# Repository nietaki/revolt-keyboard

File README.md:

[ ](https://discord.gg/myEkxF7rhV)

# Revolt Keyboard

> **Revolt** - a split ergonomic keyboard prioritising ease of adoption, flexibilty, easy build+repair, and partial upgrades
> 

## Why call it “Revolt”?

1. It’s heavily inspired by [Redox](https://github.com/mattdibi/redox-keyboard), an amazing open-source keyboard, that is still my daily driver
2. It’s revolting against the popular design philosophy of keybords like Sofle, Lily58 or Corne, which prioritise a compact footprint over other qualities
3. Some might find it “revolting”, since its looks are secondary to its features

More info on the design philosophy behind revolt in the [Revolt Manifesto](./Revolt_Manifesto.md)

## TL;DR

It’s a 68(+3) key, wired, choc-based split ergonomic keyboard running QMK. Instead of being split into 2 halves, it’s split into 3 parts: left input, right input and the center one called “commander”

The left and right input parts are “dumb”, and contain only the switches and diodes to make 7x5 matrix work, plus optional LEDs under home keys.

The case will be made with low profile + tenting in mind (with multiple tenting angles possible), with two versions: for soldered switches without a top plate and hotswap with a top plate.

The commander board should lend itself to experimenting with different pointing devices. 
Current has connectors for a PSP 3000 joystick. It should be easy to create versions that support other pointing devises, like a trackball, a Cirque touchpad or other joysticks.

## How To...

### ...build the keyboard?

Follow the [build video](https://www.youtube.com/watch?v=ghhF0bAFxww). You can find more support under the links [here](https://ntkstudio.net/products/revolt-keyboard/#support).

### ...make the cases?

The case files are available on [Printables](https://www.printables.com/model/1439208-revolt-keyboard-cases-rev1) and [Thingiverse](https://www.thingiverse.com/thing:7166363).

### ...compile the firmware?

```bash
$ cd /path/to/qmk_firmware
$ qmk compile -kb revolt/rev1 -km default
#  It should generate the firmware file
$ stat ./revolt_rev1_default.uf2
```
### ...flash the firmware?

1. Unplug the commander board
1. Push the `bootsel` button on the RP2040
1. While having the button pushed in, connect the commander board to the computer

A virtual drive (?) for the rpi should be discovered by the computer. 
Drag the compiled firmware file into it. 
RPi will reboot and run the firmware.

## FAQ

### Why do you hate Sofle/Lily58/Corne?

I don’t! They’re beautiful keyboards, designed with love and forethought, all of them with passionate communities. They just don’t fit the criteria of what I’m looking for in an ergonomic keyboard that can be used just as easily for programming and gaming, especially for people coming from “regular” keyboards. I wanted to make a keyboard that’s perfect for me and other like-minded people.

### No wireless version?

I’m not ruling out a wireless version in the future. I’d like to perfect the wired version to my liking and see what kinds of compromises make sense.

But with Revolt being open source, there’s no reason for anyone interested not to take a crack at it themselves.

## Workflow

1. Build matrix, outline and pcb in yml
2. generate kicad pcb
3. Create the kicad project
4. Replace the kicad pcb file with the generated one
5. Replace the switch footprints with the ones from keyswitch library
5. Create the matrix schematic by hand, with the diode numbers matching the swich numbers from pcb
6. **change the diode numbers in the pcb to line up with the switch numbers in the pcbnew**
  - this can be automated together with the switch numbers, I think
7. Add hierarchical net names
7. Update the schematic from the pcb band the other way until stuff is consistent.
8. ...
8. Draw the rest of the owl

## Special thanks

Projects that helped or inspired me:

- https://github.com/mattdibi/redox-keyboard
- https://github.com/daprice/keyswitches.pretty/ - adapted some footprints from this brilliant library
- https://flatfootfox.com/ergogen-introduction/
- https://github.com/labtroll/KiCad-DesignRules/tree/main
- https://docs.ergogen.xyz/
- https://github.com/sol/KiCad-RP-Pico

## License

[Revolt Keyboard](https://github.com/nietaki/revolt-keyboard)© 2024 by [@nietaki](https://nietaki.com/) is licensed under [CC BY-SA 4.0](http://creativecommons.org/licenses/by-sa/4.0/?ref=chooser-v1)

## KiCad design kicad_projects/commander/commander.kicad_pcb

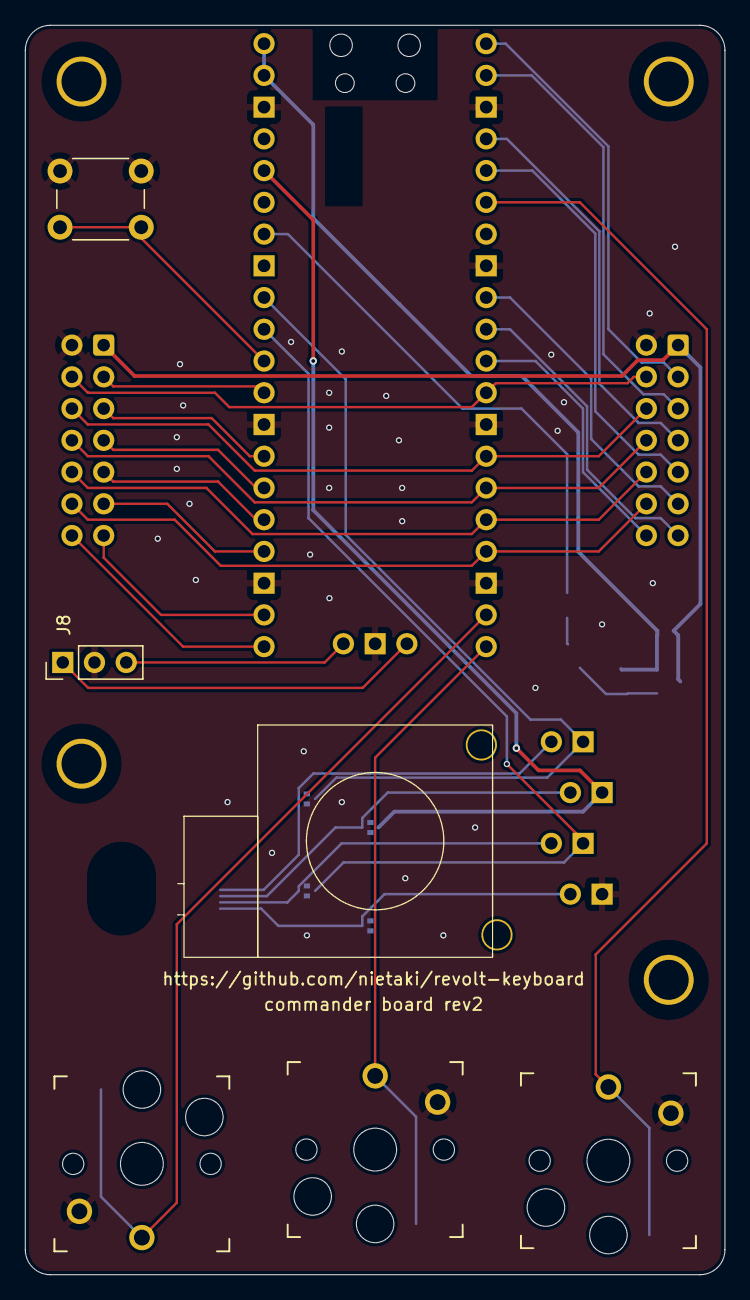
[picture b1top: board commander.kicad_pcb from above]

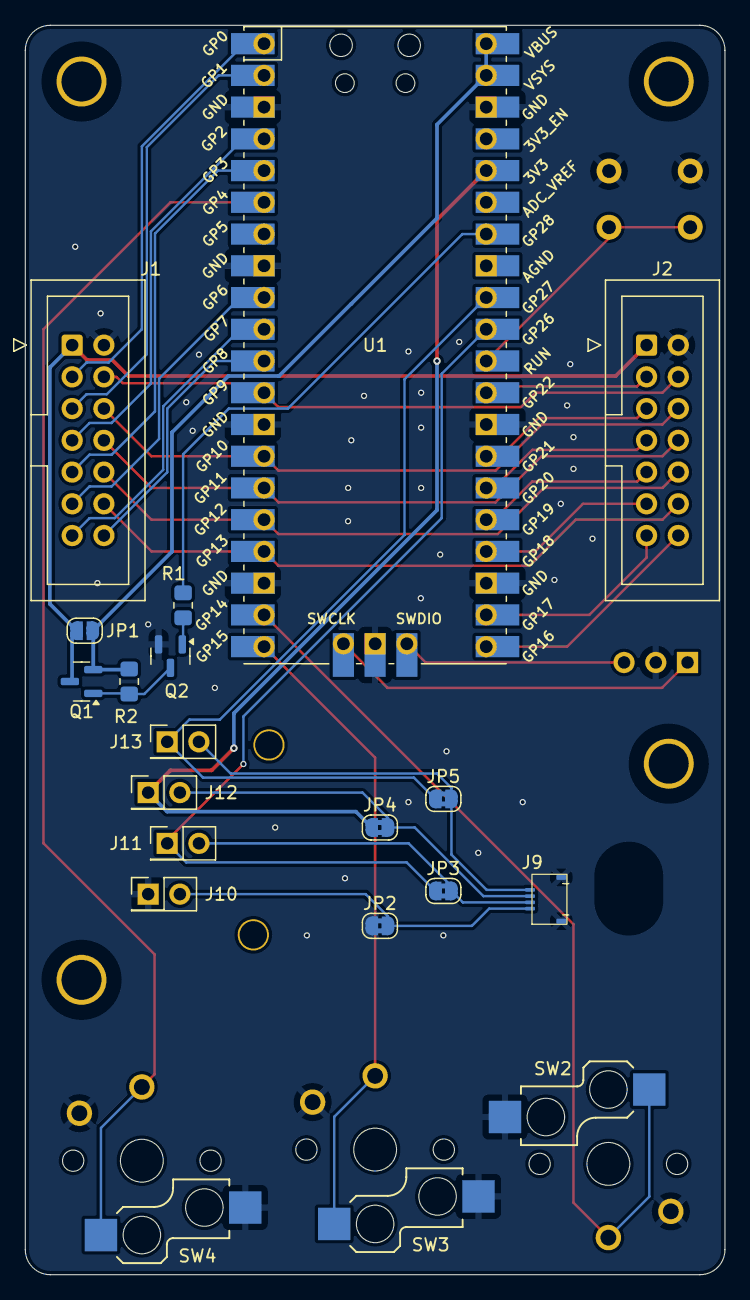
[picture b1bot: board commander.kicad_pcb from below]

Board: 2 copper layers, 56.0 x 100.0 mm, 27 parts (17 on the bottom side), 38 nets.

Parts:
HOLE_M3, HOLE_M3#2, HOLE_M3#3: H2; HOLE_M3
HOLE_M3#4: H1; HOLE_M3
J1: right input IDC14; IDC-Header_2x07_P2.54mm_Vertical
J2: left input IDC14; IDC-Header_2x07_P2.54mm_Vertical
J8: debug out; PinHeader_1x03_P2.54mm_Vertical
J9: HC-FPC-05-09-4RLTAG
J10, J11, J12, J13: Conn_02x01; PinHeader_2x01_P2.54mm_Vertical
JP1: SolderJumper_2_Open; SolderJumper-2_P1.3mm_Open_RoundedPad1.0x1.5mm
JP2, JP3, JP4, JP5: SolderJumper_2_Bridged; SolderJumper-2_P1.3mm_Bridged2Bar_RoundedPad1.0x1.5mm
PSP_JOY: PSP1000_JOY
Q1: AO3401A; SOT-23
Q2: NPN - MMBT2222A; SOT-23
R1: 1k; R_0805_2012Metric_Pad1.20x1.40mm_HandSolder
R2: 10k; R_0805_2012Metric_Pad1.20x1.40mm_HandSolder
SW1: RESET_SWITCH; SW_PUSH_6mm_H4.3mm
SW2, SW3, SW4: SW_Push; Kailh_socket_PG1350_optional
U1: Pico; RPi_Pico_SMD_TH

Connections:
3V3: J12.1, JP4.1 (A), U1.36 (3V3)
5V: JP1.1 (A), Q1.2 (S), R2.2, U1.39 (VSYS), U1.40 (VBUS)
/COL0: J2.3, U1.29 (GPIO22)
/COL1: J2.5, U1.27 (GPIO21)
/COL2: J2.7, U1.26 (GPIO20)
/COL3: J2.9, U1.25 (GPIO19)
/COL4: J2.11, U1.24 (GPIO18)
/COL5: J2.13, U1.22 (GPIO17)
/COL6: J2.14, U1.21 (GPIO16)
/COL7: J1.14, U1.11 (GPIO8)
/COL8: J1.13, U1.10 (GPIO7)
/COL9: J1.11, U1.9 (GPIO6)
/COL10: J1.9, U1.5 (GPIO3)
/COL11: J1.7, U1.4 (GPIO2)
/COL12: J1.5, U1.2 (GPIO1)
/COL13: J1.3, U1.1 (GPIO0)
/LED_ENABLE: R1.2, U1.34 (GPIO28_ADC2)
/LMB: SW2.1, U1.19 (GPIO14)
/MMB: SW3.1, U1.20 (GPIO15)
/RMB: SW4.1, U1.6 (GPIO4)
/ROW0: J1.12, J2.12, U1.17 (GPIO13)
/ROW1: J1.10, J2.10, U1.16 (GPIO12)
/ROW2: J1.8, J2.8, U1.15 (GPIO11)
/ROW3: J1.6, J2.6, U1.14 (GPIO10)
/ROW4: J1.4, J2.4, U1.12 (GPIO9)
/RUN: SW1.2, U1.30 (RUN)
/X1: J11.1, JP3.1 (A), U1.31 (GPIO26_ADC0)
/X2: J13.1, JP5.1 (A), U1.32 (GPIO27_ADC1)
GND: J1.2, J2.2, J8.2, J9.5 (P1), J9.6 (P2), J10.1, JP2.1 (A), Q2.2 (E), SW1.1, SW2.2, SW3.2, SW4.2, U1.3 (GND), U1.8 (GND), U1.13 (GND), U1.18 (GND), U1.23 (GND), U1.28 (GND), U1.38 (GND), U1.42 (GND)
LED_5V: J1.1, J2.1, JP1.2 (B), Q1.3 (D)
unnamed: J8.1, U1.41 (SWCLK)
unnamed: J8.3, U1.43 (SWDIO)
unnamed: J9.1, J10.2, JP2.2 (B)
unnamed: J9.2, J11.2, JP3.2 (B)
unnamed: J9.3, J12.2, JP4.2 (B)
unnamed: J9.4, J13.2, JP5.2 (B)
unnamed: Q1.1 (G), Q2.3 (C), R2.1
unnamed: Q2.1 (B), R1.1

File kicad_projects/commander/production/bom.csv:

Designator,Footprint,Quantity,Value,LCSC Part #
J1,IDC-Header_2x07_P2.54mm_Vertical,1,right input IDC14,
"J10, J11, J12, J13",PinHeader_2x01_P2.54mm_Vertical,4,Conn_02x01,
J2,IDC-Header_2x07_P2.54mm_Vertical,1,left input IDC14,
J8,PinHeader_1x03_P2.54mm_Vertical,1,debug out,
J9,HC-FPC-05-09-4RLTAG,1,522710469,
JP1,SolderJumper-2_P1.3mm_Open_RoundedPad1.0x1.5mm,1,SolderJumper_2_Open,
PSP_JOY,PSP1000_JOY,1,PSP1000_JOY,
Q1,SOT-23,1,AO3401A,C15127
Q2,SOT-23,1,NPN - MMBT2222A,C8512
R1,0805,1,1k,
R2,0805,1,10k,
SW1,SW_PUSH_6mm_H4.3mm,1,RESET_SWITCH,
"SW2, SW3, SW4",Kailh_socket_PG1350_optional,3,SW_Push,
U1,RPi_Pico_SMD_TH,1,Pico,

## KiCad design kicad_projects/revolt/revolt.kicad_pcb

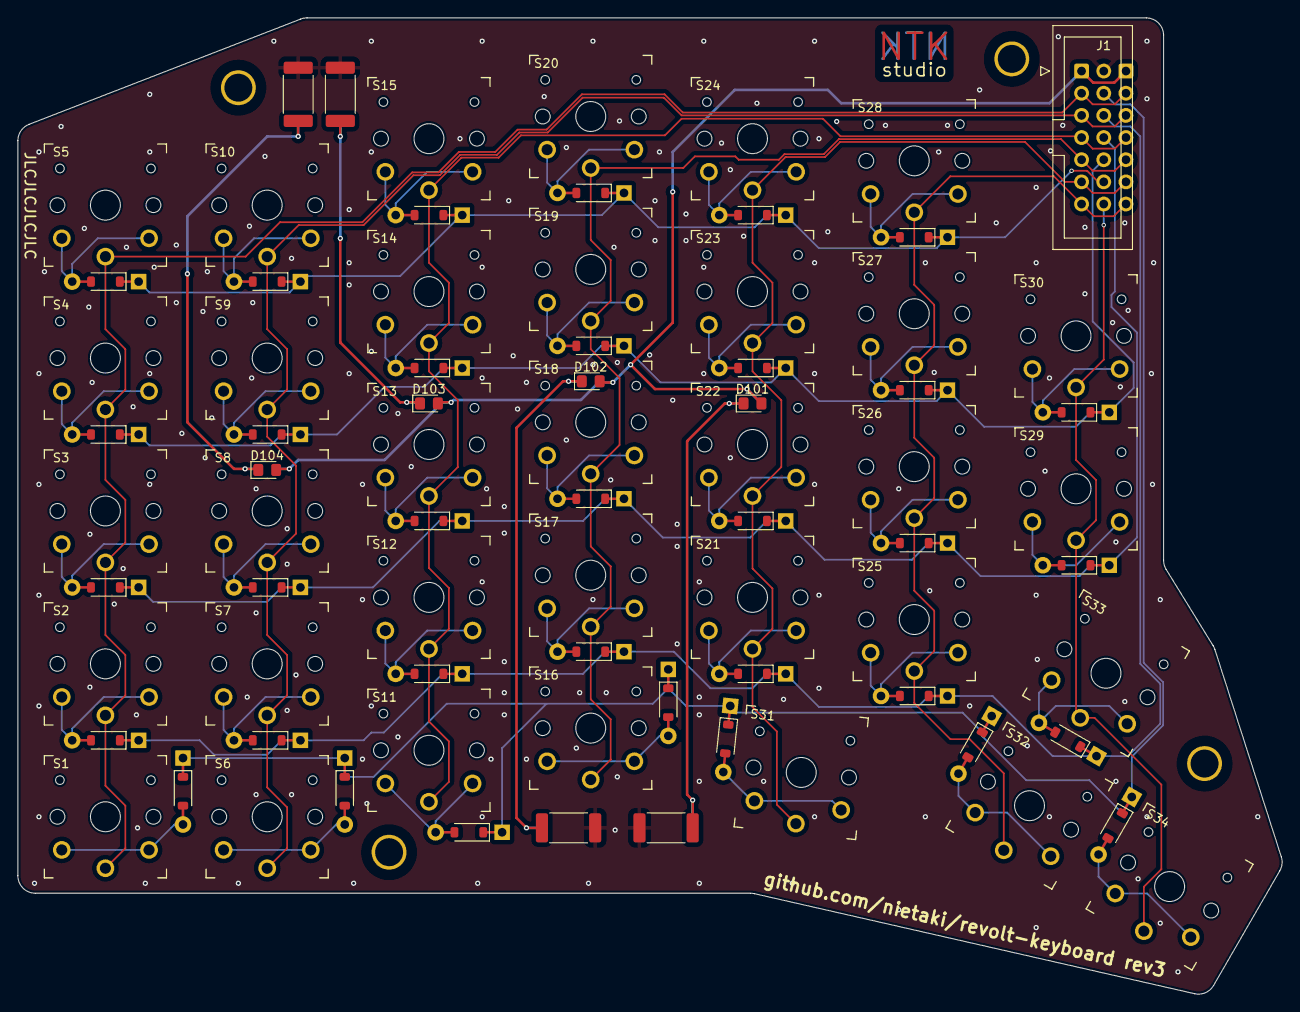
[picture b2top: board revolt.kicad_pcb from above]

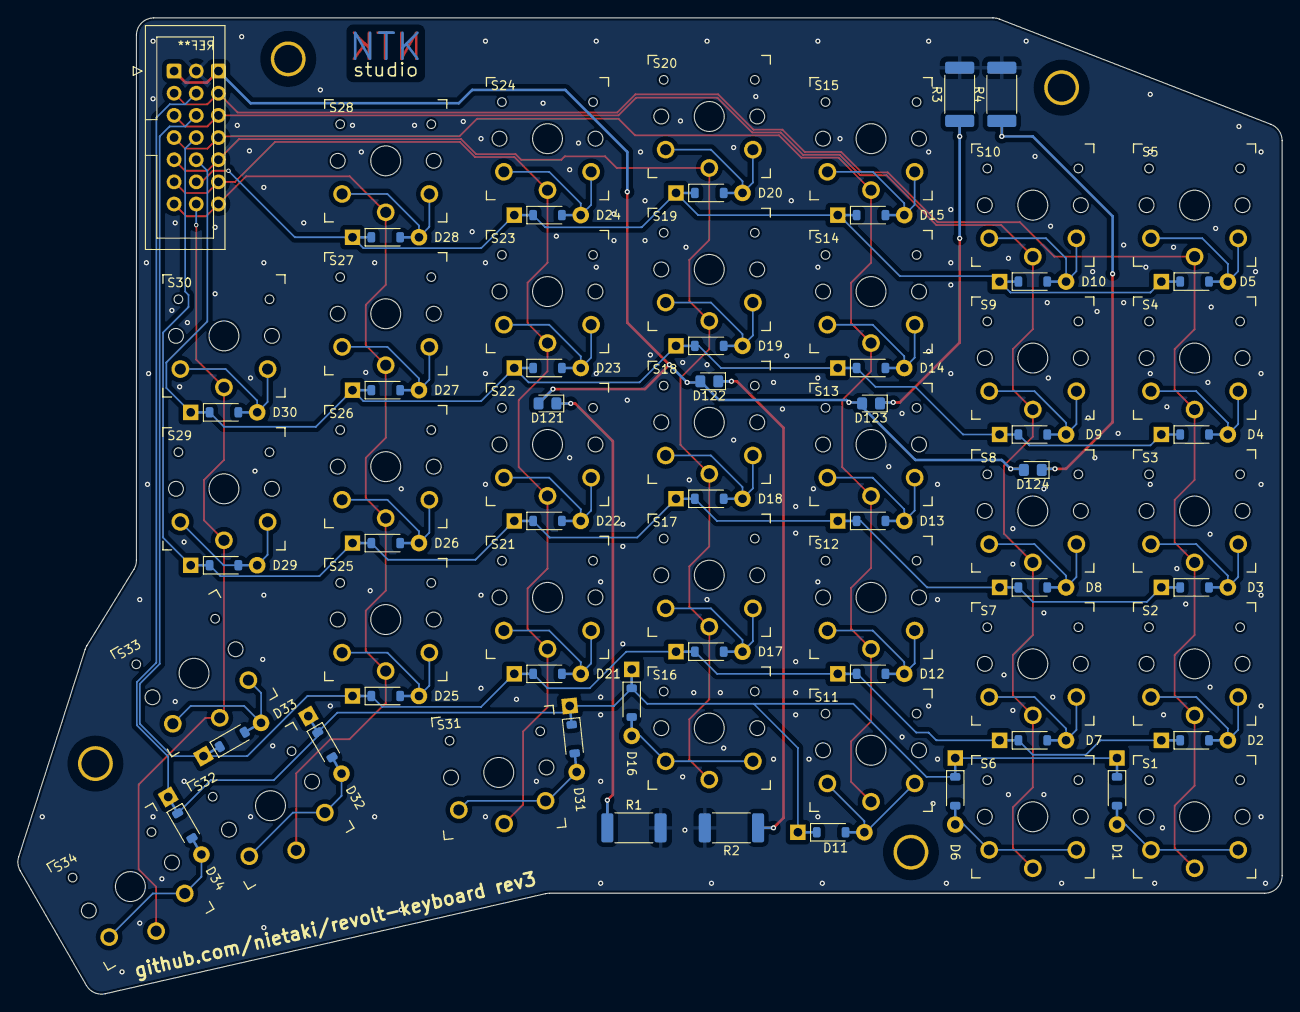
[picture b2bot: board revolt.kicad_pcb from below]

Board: 2 copper layers, 144.9 x 111.9 mm, 85 parts (42 on the bottom side), 52 nets.

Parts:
D1, D2, D3, D4, D5, D6, D7, D8, D9, D10, D11, D12, D13, D14, D15, D16, D17, D18, D19, D20, D21, D22, D23, D24, D25, D26, D27, D28, D29, D30, D31, D32, D33, D34: D_SOD-123-combo-reversible
D101, D102, D103, D104, D121, D122, D123, D124: LED; LED_0805_2012Metric_Pad1.15x1.40mm_HandSolder
H1, H2, H3, H4: MountingHole; HOLE_M3
J1: IDC-Header_2x07_P2.54mm_Vertical_Reversible
R1, R2, R3, R4: 150; R_2512_6332Metric_Pad1.40x3.35mm_HandSolder_reversible
S1, S2, S3, S4, S5, S6, S7, S8, S9, S10, S11, S12, S13, S14, S15, S16, S17, S18, S19, S20, S21, S22, S23, S24, S25, S26, S27, S28, S29, S30, S31, S32, S33, S34: SW_PG1350_reversible_with_keycap_outline

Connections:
5V: D101.2 (A), D102.2 (A), D103.2 (A), D104.2 (A), D121.2 (A), D122.2 (A), D123.2 (A), D124.2 (A), J1.1
/COL0: J1.3, S1.1, S2.1, S3.1, S4.1, S5.1
/COL1: J1.5, S6.1, S7.1, S8.1, S9.1, S10.1
/COL2: J1.7, S11.1, S12.1, S13.1, S14.1, S15.1
/COL3: J1.9, S16.1, S17.1, S18.1, S19.1, S20.1
/COL4: J1.11, S21.1, S22.1, S23.1, S24.1, S31.1
/COL5: J1.13, S25.1, S26.1, S27.1, S28.1, S32.1
/COL6: J1.14, S29.1, S30.1, S33.1, S34.1
/ROW0: D5.1 (K), D10.1 (K), D15.1 (K), D20.1 (K), D24.1 (K), D28.1 (K), J1.12
/ROW1: D4.1 (K), D9.1 (K), D14.1 (K), D19.1 (K), D23.1 (K), D27.1 (K), D30.1 (K), J1.10
/ROW2: D3.1 (K), D8.1 (K), D13.1 (K), D18.1 (K), D22.1 (K), D26.1 (K), D29.1 (K), J1.8
/ROW3: D2.1 (K), D7.1 (K), D12.1 (K), D17.1 (K), D21.1 (K), D25.1 (K), D33.1 (K), J1.6
/ROW4: D1.1 (K), D6.1 (K), D11.1 (K), D16.1 (K), D31.1 (K), D32.1 (K), D34.1 (K), J1.4
GND: J1.2, R1.2, R2.2, R3.2, R4.2
unnamed: D1.2 (A), S1.2
unnamed: D2.2 (A), S2.2
unnamed: D3.2 (A), S3.2
unnamed: D4.2 (A), S4.2
unnamed: D5.2 (A), S5.2
unnamed: D6.2 (A), S6.2
unnamed: D7.2 (A), S7.2
unnamed: D8.2 (A), S8.2
unnamed: D9.2 (A), S9.2
unnamed: D10.2 (A), S10.2
unnamed: D11.2 (A), S11.2
unnamed: D12.2 (A), S12.2
unnamed: D13.2 (A), S13.2
unnamed: D14.2 (A), S14.2
unnamed: D15.2 (A), S15.2
unnamed: D16.2 (A), S16.2
unnamed: D17.2 (A), S17.2
unnamed: D18.2 (A), S18.2
unnamed: D19.2 (A), S19.2
unnamed: D20.2 (A), S20.2
unnamed: D21.2 (A), S21.2
unnamed: D22.2 (A), S22.2
unnamed: D23.2 (A), S23.2
unnamed: D24.2 (A), S24.2
unnamed: D25.2 (A), S25.2
unnamed: D26.2 (A), S26.2
unnamed: D27.2 (A), S27.2
unnamed: D28.2 (A), S28.2
unnamed: D29.2 (A), S29.2
unnamed: D30.2 (A), S30.2
unnamed: D31.2 (A), S31.2
unnamed: D32.2 (A), S32.2
unnamed: D33.2 (A), S33.2
unnamed: D34.2 (A), S34.2
unnamed: D101.1 (K), D121.1 (K), R1.1
unnamed: D102.1 (K), D122.1 (K), R2.1
unnamed: D103.1 (K), D123.1 (K), R3.1
unnamed: D104.1 (K), D124.1 (K), R4.1

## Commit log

2024-02-21 add ergogen boilerplate
2024-02-22 Initial ergogen layout, from scratch
2024-02-24 Choc layout looking ok
2024-02-25 I forgot to commit yesterday
2024-02-25 Moving things around a bit, screws roughly valid now
2024-02-25 PCB first tries
2024-02-25 kicad project, no schematic
2024-02-26 add matrix to the schematic, minus the net names
2024-02-26 Update the diode numbers
2024-02-26 fix pcb diode numbers
2024-02-26 fixed pcb and schematic
2024-02-26 todos, remove fp info cache
2024-02-27 Add design rules (in more ways than one)
2024-02-29 Add library with custom footprints
2024-03-01 Make the outline universal for hotswap and regular switches
2024-03-02 Finalize the pcb dimensions
2024-03-02 Add a reversible diode footprint for keyboards with top plate
2024-03-04 Base design, need to unify and double-check DRD rules
2024-03-06 Improved diodes, LED schematic
2024-03-06 Final footprints, schematic fixes, LEDs positioned
2024-03-07 Start routing the board
2024-03-07 Route everything but the ground plane
2024-03-08 Ground plane and stitching
2024-03-08 Add the url on the silkscreen, more stitching
2024-03-08 Cosmetic changes
2024-03-10 Commander board
2024-03-10 Commander board passing DRC
2024-03-10 Add silkscreen info, some more routing
2024-03-11 Clean up some vias, 0.25mm spacing of power nets for cleaner zone fills
2024-03-11 Port over the Revolt Manifesto from Notion
2024-03-11 Add the license
2024-04-02 Replace a relay with a MOSFET (like a pro)
2024-04-08 Production files generation
2025-05-14 big commander WIP
2025-05-15 trackpoint socket footprints
2025-05-25 WIP on the new footprint
2025-05-26 commander board rev2, pre-manufacture
2025-05-26 commander rev2 production files
2025-07-31 Correct Column net names
2025-08-04 Leave some notes on flashing the firmware
2025-10-27 Update to the latest files
2025-12-03 Update the readme and the images
2025-12-03 add shields
2025-12-03 Update shields to look slightly nicer
2025-12-05 Add build and case info
